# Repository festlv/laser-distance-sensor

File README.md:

Laser distance sensor
-----------------------

Firmware and hardware design for short-range laser distance sensor.

Preliminary feature list:
  
  * Based on [ST VL53L0X ToF distance sensor](http://www.st.com/en/imaging-and-photonics-solutions/vl53l0x.html),
  * Multiple ranging profiles/modes (default, high accuracy, long range),
  * Up to 2m range (indoors) in long range mode,
  * +/- 3mm accuracy (indoors) in hight accuracy mode,
  * On-board power regulation for 3.3-5.5V input,
  * On-board microcontroller [STM32F042](http://www.st.com/en/microcontrollers/stm32f042f6.html)
  * USB (CDC) and TTL serial outputs,
  * 24x24mm size, M3 mounting holes.

HERE BE DRAGONS
===================

This project is WIP. Specs might be inaccurate, hardware might let out smoke,
firmware might not compile.

Current status
=================

Hardware: first prototypes have been ordered.
Firmware: waiting on hardware.

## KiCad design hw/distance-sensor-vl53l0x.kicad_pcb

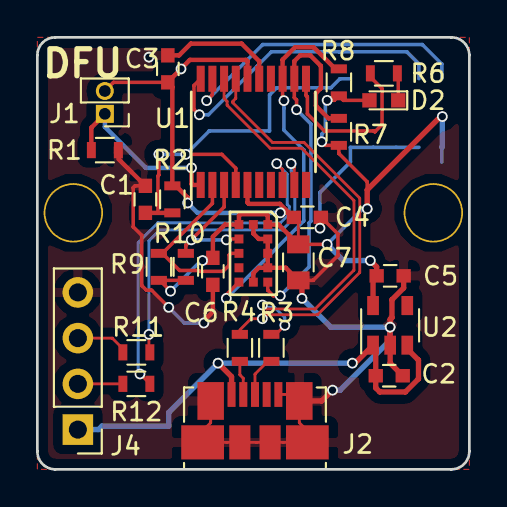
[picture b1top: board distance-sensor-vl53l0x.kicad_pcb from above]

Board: 2 copper layers, 24.0 x 24.0 mm, 28 parts (1 on the bottom side), 21 nets.

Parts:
C1, C3, C6: 0.1uF; C_0603
C2, C4, C5: 1uF; C_0603
C7: 4.7uF; C_0805
D2: LED; LED_0603
J1: DFU; Pin_Header_Straight_1x02_Pitch1.27mm
J2: USB_OTG; USB_Micro-B_Molex_47346-0001
J3: CONN_02X05; Pin_Header_1.27mm_2x5
J4: UART; Pin_Header_Straight_1x04_Pitch2.54mm
J101, J102: TEST_1P; Mounting_hole_3mm
R1, R2, R7, R8, R9, R10: 4K7; R_0603
R3, R4: 22R; R_0603
R6, R11, R12: 220R; R_0603
U1: STM32F042F6Px; TSSOP-20_4.4x6.5mm_Pitch0.65mm
U2: MIC5504-3.3; SOT-23-5
U3: VL53L0X

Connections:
+3.3V: C3.1, C4.1, C5.1, C6.1, C7.1, D2.2, J1.2, J3.1, R2.1, R7.1, R8.1, R9.1, R10.1, U1.5, U1.16, U2.5, U3.1, U3.11
+5V: C2.1, J2.1, J4.1, U2.1, U2.3
/BOOT0: J1.1, R1.1, U1.1
/I2C_INT: R8.2, U1.13, U3.7
/I2C_RST: R7.2, U1.12, U3.5
/NRST: C1.1, J3.10, R2.2, U1.4
/SCL: R10.2, U1.3, U3.10
/SDA: R9.2, U1.2, U3.9
/SWCLK: J3.4, U1.20
/SWDIO: J3.2, U1.19
/USART_RX: R11.1, U1.9
/USART_TX: R12.1, U1.8
/USB_D_N: R4.1, U1.17
/USB_D_P: R3.1, U1.18
GND: C1.2, C2.2, C3.2, C4.2, C5.2, C6.2, C7.2, J2.5, J2.6, J3.3, J3.5, J3.7, J3.9, J4.4, R1.2, U1.15, U2.2, U3.2, U3.3, U3.4, U3.6, U3.12
unnamed: D2.1, R6.1
unnamed: J2.2, R4.2
unnamed: J2.3, R3.2
unnamed: J4.2, R12.2
unnamed: J4.3, R11.2
unnamed: R6.2, U1.11

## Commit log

2017-04-24 Rev1 hardware ordered
2017-04-24 Adds README, LICENSE and PCB render.
2017-04-24 Rearranged schematics, PDF output for easier viewing
2017-08-24 Integrates VL53L0X driver
2017-08-26 Add an initial, fully working firmware
2017-09-09 Hardware changes for rev2
2017-12-28 Change PCB corners to rounded.
